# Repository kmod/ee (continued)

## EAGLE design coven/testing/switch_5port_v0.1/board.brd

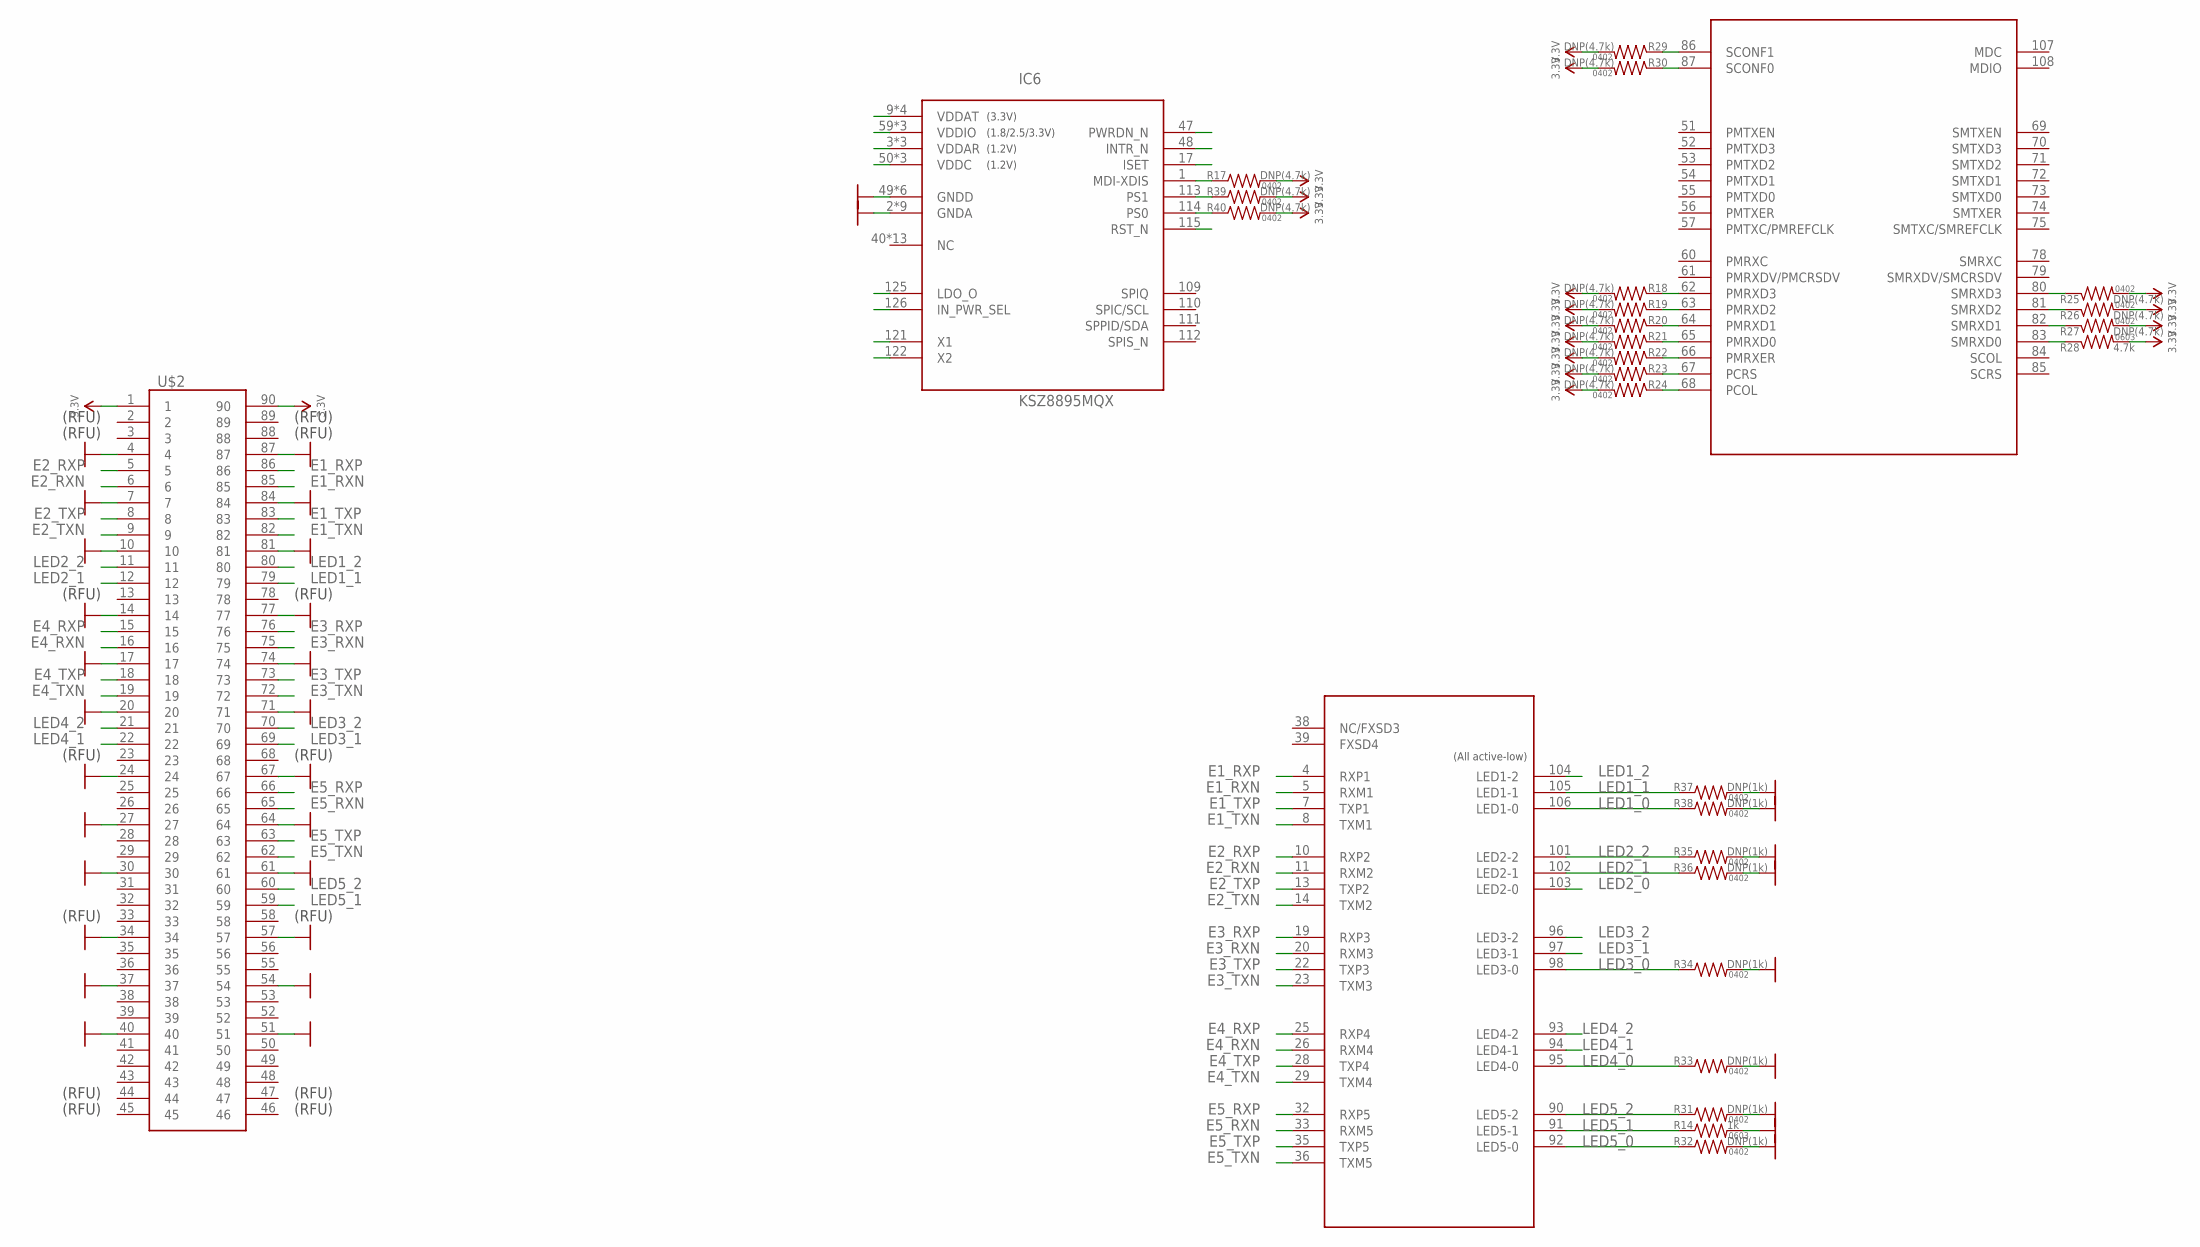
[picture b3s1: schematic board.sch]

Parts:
IC6: KSZ8895MQX; PQFP-128
R14: 1k; 0603-RES
R17, R18, R19, R20, R21, R22, R23, R24, R25, R26, R27, R29, R30, R39, R40: DNP(4.7k); 0402-RES
R28: 4.7k; 0603-RES
R31, R32, R33, R34, R35, R36, R37, R38: DNP(1k); 0402-RES
U$2: DF40-90HDR; DF40-HDR-90

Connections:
3.3V: R17.2, R18.2, R19.2, R20.2, R21.2, R22.2, R23.2, R24.2, R25.2, R26.2, R27.2, R28.2, R29.2, R30.2, R39.2, R40.2, U$2.1, U$2.90
E1_RXN: IC6.5 (RXM1), U$2.85
E1_RXP: IC6.4 (RXP1), U$2.86
E1_TXN: IC6.8 (TXM1), U$2.82
E1_TXP: IC6.7 (TXP1), U$2.83
E2_RXN: IC6.11 (RXM2), U$2.6
E2_RXP: IC6.10 (RXP2), U$2.5
E2_TXN: IC6.14 (TXM2), U$2.9
E2_TXP: IC6.13 (TXP2), U$2.8
E3_RXN: IC6.20 (RXM3), U$2.75
E3_RXP: IC6.19 (RXP3), U$2.76
E3_TXN: IC6.23 (TXM3), U$2.72
E3_TXP: IC6.22 (TXP3), U$2.73
E4_RXN: IC6.26 (RXM4), U$2.16
E4_RXP: IC6.25 (RXP4), U$2.15
E4_TXN: IC6.29 (TXM4), U$2.19
E4_TXP: IC6.28 (TXP4), U$2.18
E5_RXN: IC6.33 (RXM5), U$2.65
E5_RXP: IC6.32 (RXP5), U$2.66
E5_TXN: IC6.36 (TXM5), U$2.62
E5_TXP: IC6.35 (TXP5), U$2.63
GND: IC6.2 (GNDA), IC6.6 (GNDA), IC6.12 (GNDA), IC6.16 (GNDA), IC6.21 (GNDA), IC6.27 (GNDA), IC6.30 (GNDA), IC6.34 (GNDA), IC6.49 (GNDD), IC6.58 (GNDD), IC6.76 (GNDD), IC6.88 (GNDD), IC6.99 (GNDD), IC6.116 (GNDD), IC6.127 (GNDA), R14.2, R31.2, R32.2, R33.2, R34.2, R35.2, R36.2, R37.2, R38.2, U$2.4, U$2.7, U$2.10, U$2.14, U$2.17, U$2.20, U$2.24, U$2.27, U$2.30, U$2.34, U$2.37, U$2.40, U$2.51, U$2.54, U$2.57, U$2.61, U$2.64, U$2.67, U$2.71, U$2.74, U$2.77, U$2.81, U$2.84, U$2.87
LED1_0: IC6.106 (LED1-0), R38.1
LED1_1: IC6.105 (LED1-1), R37.1, U$2.79
LED1_2: IC6.104 (LED1-2), U$2.80
LED2_0: IC6.103 (LED2-0)
LED2_1: IC6.102 (LED2-1), R36.1, U$2.12
LED2_2: IC6.101 (LED2-2), R35.1, U$2.11
LED3_0: IC6.98 (LED3-0), R34.1
LED3_1: IC6.97 (LED3-1), U$2.69
LED3_2: IC6.96 (LED3-2), U$2.70
LED4_0: IC6.95 (LED4-0), R33.1
LED4_1: IC6.94 (LED4-1), U$2.22
LED4_2: IC6.93 (LED4-2), U$2.21
LED5_0: IC6.92 (LED5-0), R32.1
LED5_1: IC6.91 (LED5-1), R14.1, U$2.59
LED5_2: IC6.90 (LED5-2), R31.1, U$2.60
unnamed: IC6.1 (MDI-XDIS), R17.1
unnamed: IC6.62 (PMRXD3), R18.1
unnamed: IC6.63 (PMRXD2), R19.1
unnamed: IC6.64 (PMRXD1), R20.1
unnamed: IC6.65 (PMRXD0), R21.1
unnamed: IC6.66 (PMRXER), R22.1
unnamed: IC6.67 (PCRS), R23.1
unnamed: IC6.68 (PCOL), R24.1
unnamed: IC6.80 (SMRXD3), R25.1
unnamed: IC6.81 (SMRXD2), R26.1
unnamed: IC6.82 (SMRXD1), R27.1
unnamed: IC6.83 (SMRXD0), R28.1
unnamed: IC6.86 (SCONF1), R29.1
unnamed: IC6.87 (SCONF0), R30.1
unnamed: IC6.113 (PS1), R39.1
unnamed: IC6.114 (PS0), R40.1
unnamed: IC6.50 (VDDC), IC6.89 (VDDC), IC6.117 (VDDC)
unnamed: IC6.3 (VDDAR), IC6.15 (VDDAR), IC6.31 (VDDAR)
unnamed: IC6.59 (VDDIO), IC6.77 (VDDIO), IC6.100 (VDDIO)
unnamed: IC6.9 (VDDAT), IC6.18 (VDDAT), IC6.24 (VDDAT), IC6.37 (VDDAT)

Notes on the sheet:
(RFU)

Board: 4 copper layers, 27 parts (1 on the bottom side), 56 nets, no tracks yet.

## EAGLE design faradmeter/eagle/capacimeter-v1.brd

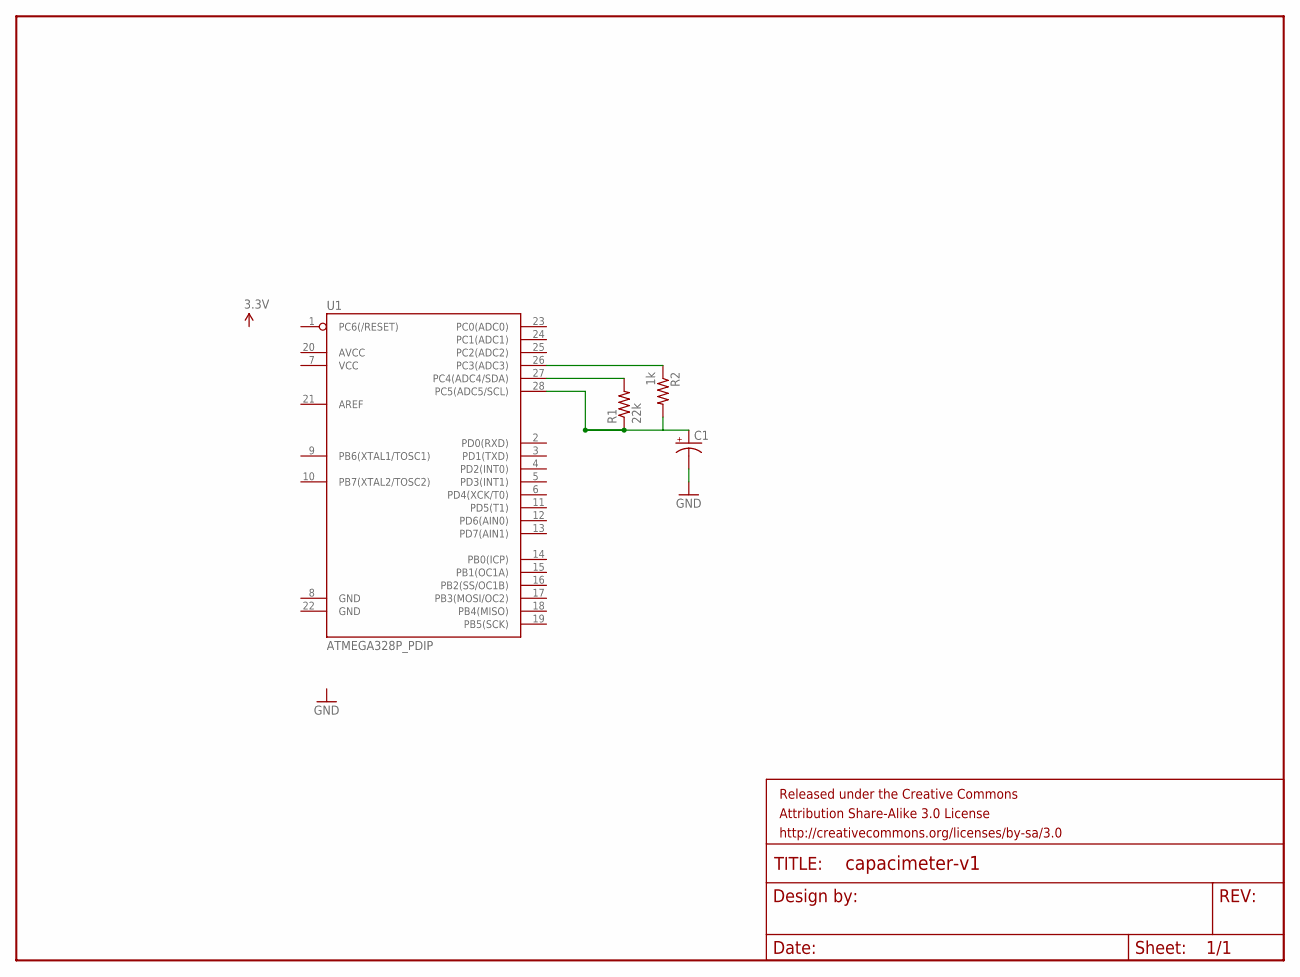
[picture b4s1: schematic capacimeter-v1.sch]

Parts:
C1: CAP_POL1206; EIA3216
FRAME1: FRAME-LETTER; CREATIVE_COMMONS
R1: 22k; 0603-RES
R2: 1k; 0603-RES
U1: ATMEGA328P_PDIP; DIL28-3

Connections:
GND: C1.C (-)
unnamed: R1.2, U1.27 (PC4(ADC4/SDA))
unnamed: C1.A (+), R1.1, R2.2, U1.28 (PC5(ADC5/SCL))
unnamed: R2.1, U1.26 (PC3(ADC3))

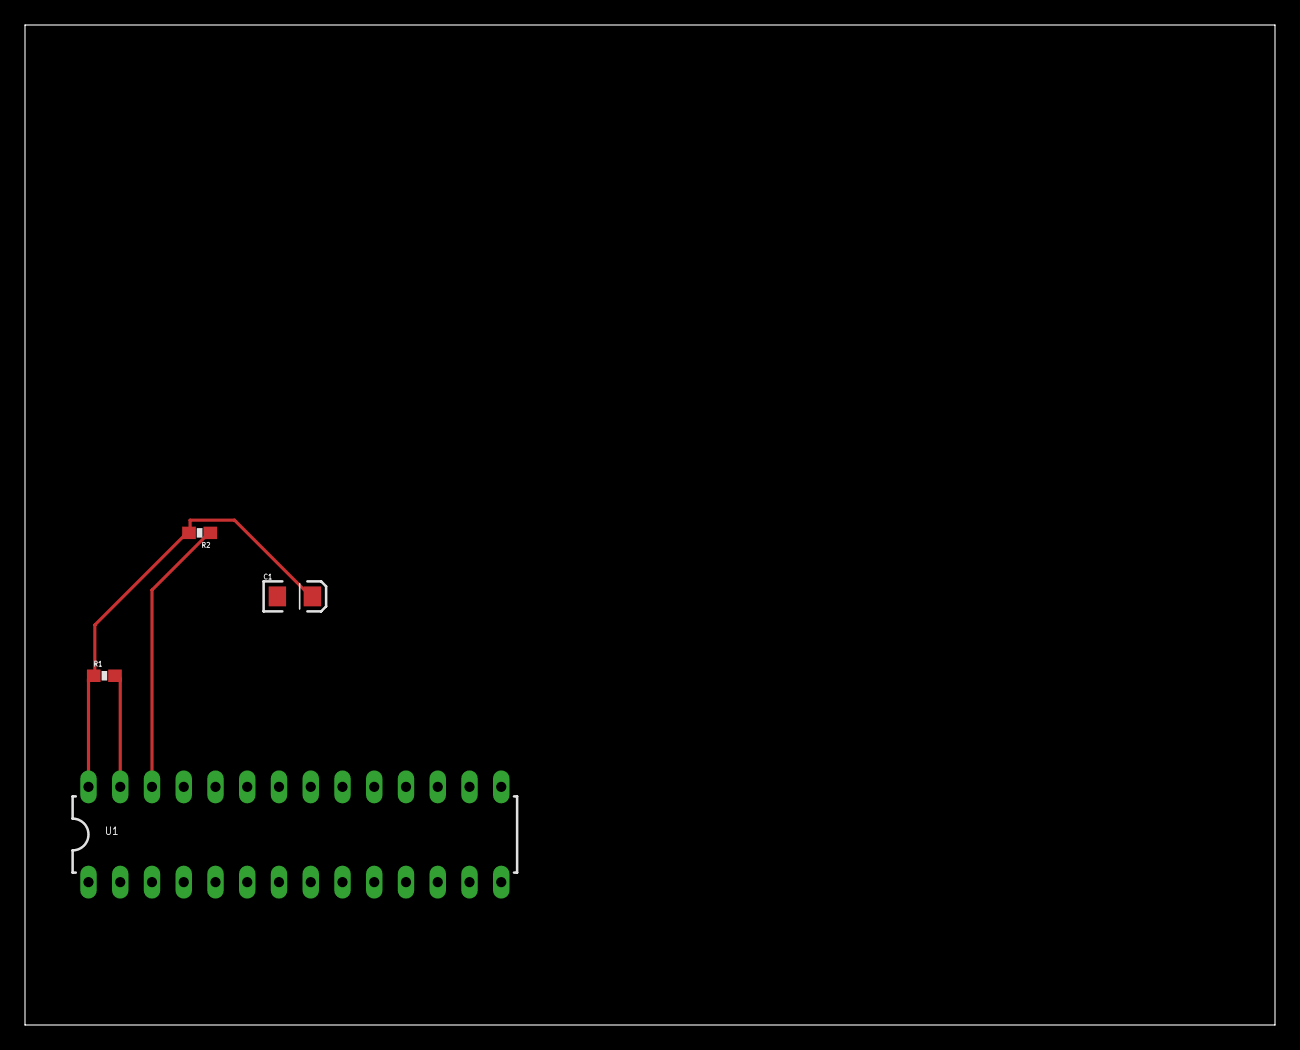
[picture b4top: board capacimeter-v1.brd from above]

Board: 2 copper layers, 100.0 x 80.0 mm, 5 parts (0 on the bottom side), 3 nets.

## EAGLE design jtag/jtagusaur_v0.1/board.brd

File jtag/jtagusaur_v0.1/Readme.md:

simple MB jtag board; bad footprint, use 0.1a instead

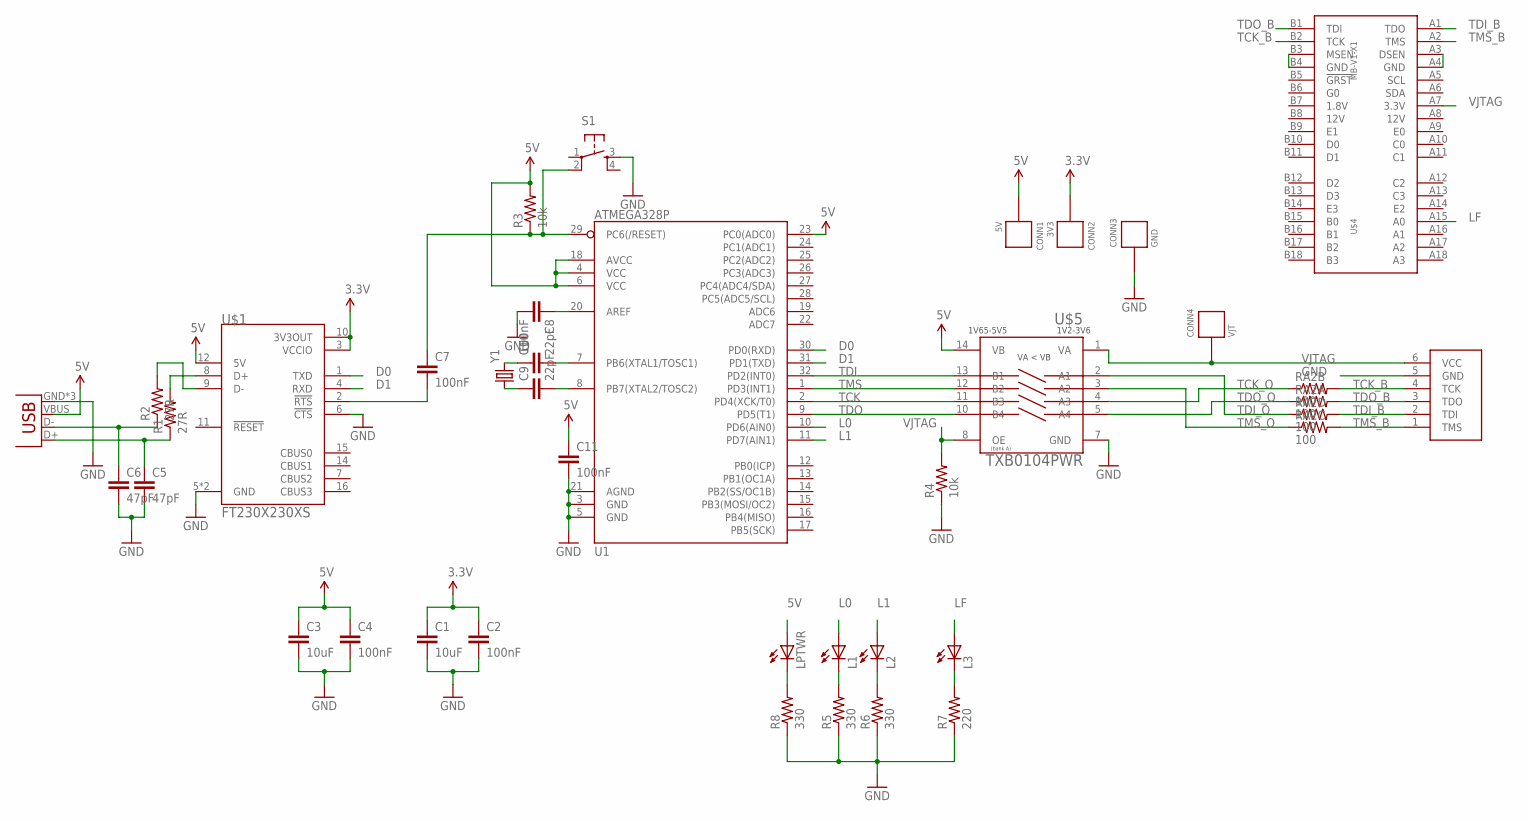
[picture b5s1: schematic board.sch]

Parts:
C1, C3: 10uF; 0805
C2, C4, C7, C8, C11: 100nF; 0402-CAP
C5, C6: 47pF; 0402-CAP
C9, C10: 22pF; 0402-CAP
CONN1: 5V; HOLE_22AWG
CONN2: 3V3; HOLE_22AWG
CONN3: GND; HOLE_22AWG
CONN4: VJT; HOLE_22AWG
JP1: USB-MICROB
L1, L2, L3: LED0603; 0603_LED
LPTWR: LED0603; 0603_LED
R1, R2: 27R; 0603-RES
R3, R4: 10k; 0603-RES
R5, R6, R8: 330; 0603-RES
R7: 220; 0603-RES
RA2: 100; 0603-ARV
S1: TAC_SWITCHPTH; TACTILE-PTH
U1: ATMEGA328P; TQFP32-08
U$1: FT230X230XS; SO16
U$2: JTAGDIGILENT; 1X06
U$4: MB-V1-X1; PCIE-X1-EDGE
U$5: TXB0104PWR; TSSOP14
Y1: CRYSTALHC49US; HC49US

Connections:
3.3V: C1.1, C2.1, CONN2.P, U$1.3 (VCCIO), U$1.10 (3V3OUT)
5V: C3.1, C4.1, C11.1, CONN1.P, JP1.VBUS, LPTWR.A, R3.2, U1.4 (VCC), U1.6 (VCC), U1.18 (AVCC), U1.23 (PC0(ADC0)), U$1.12 (5V), U$5.14 (VB)
D0: U1.30 (PD0(RXD)), U$1.1 (TXD)
D1: U1.31 (PD1(TXD)), U$1.4 (RXD)
GND: C1.2, C2.2, C3.2, C4.2, C5.2, C6.2, C8.2, C11.2, CONN3.P, JP1.GND, JP1.MT1 (GND), JP1.MT2 (GND), R4.1, R5.1, R6.1, R7.1, R8.1, S1.3, U1.3 (GND), U1.5 (GND), U1.21 (AGND), U$1.5 (GND), U$1.6 (!CTS), U$1.13 (GND), U$2.5 (GND), U$4.A3 (DSEN), U$4.A4 (GND), U$4.B3 (MSEN), U$4.B4 (GND)
L0: L1.A, U1.10 (PD6(AIN0))
L1: L2.A, U1.11 (PD7(AIN1))
LF: L3.A, U$4.A15 (A0)
LPWR: LPTWR.C, R8.2
unnamed: R1.2, U$1.8 (D+)
unnamed: R2.2, U$1.9 (D-)
unnamed: C6.1, JP1.D-, R2.1
unnamed: C5.1, JP1.D+, R1.1
unnamed: C7.2, U$1.2 (!RTS)
unnamed: C7.1, R3.1, S1.2, U1.29 (PC6(/RESET))
unnamed: C10.2, U1.7 (PB6(XTAL1/TOSC1))
unnamed: C8.1, U1.20 (AREF)
unnamed: C10.1, Y1.2
unnamed: C9.2, U1.8 (PB7(XTAL2/TOSC2))
unnamed: C9.1, Y1.1
unnamed: L1.C, R5.2
unnamed: L2.C, R6.2
unnamed: L3.C, R7.2
TCK: U1.2 (PD4(XCK/T0)), U$5.11 (B3)
TCK_B: RA2.7 (2), U$2.4 (TCK), U$4.B2 (TCK)
TCK_O: RA2.2 (1), U$5.4 (A3)
TDI: U1.32 (PD2(INT0)), U$5.13 (B1)
TDI_B: RA2.5 (2), U$2.2 (TDI), U$4.A1 (TDO)
TDI_O: RA2.4 (1), U$5.2 (A1)
TDO: U1.9 (PD5(T1)), U$5.10 (B4)
TDO_B: RA2.8 (2), U$2.3 (TDO), U$4.B1 (TDI)
TDO_O: RA2.1, U$5.5 (A4)
TMS: U1.1 (PD3(INT1)), U$5.12 (B2)
TMS_B: RA2.6 (2), U$2.1 (TMS), U$4.A2 (TMS)
TMS_O: RA2.3 (1), U$5.3 (A2)
VJTAG: CONN4.P, R4.2, U$2.6 (VCC), U$4.A7 (3.3V), U$5.1 (VA)

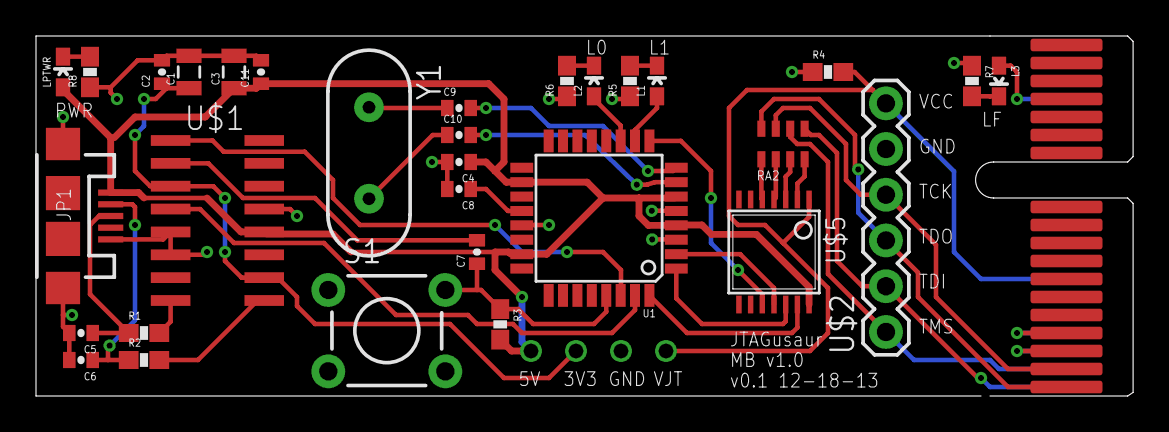
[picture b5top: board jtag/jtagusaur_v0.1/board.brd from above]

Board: 2 copper layers, 61.0 x 20.0 mm, 36 parts (0 on the bottom side), 36 nets.

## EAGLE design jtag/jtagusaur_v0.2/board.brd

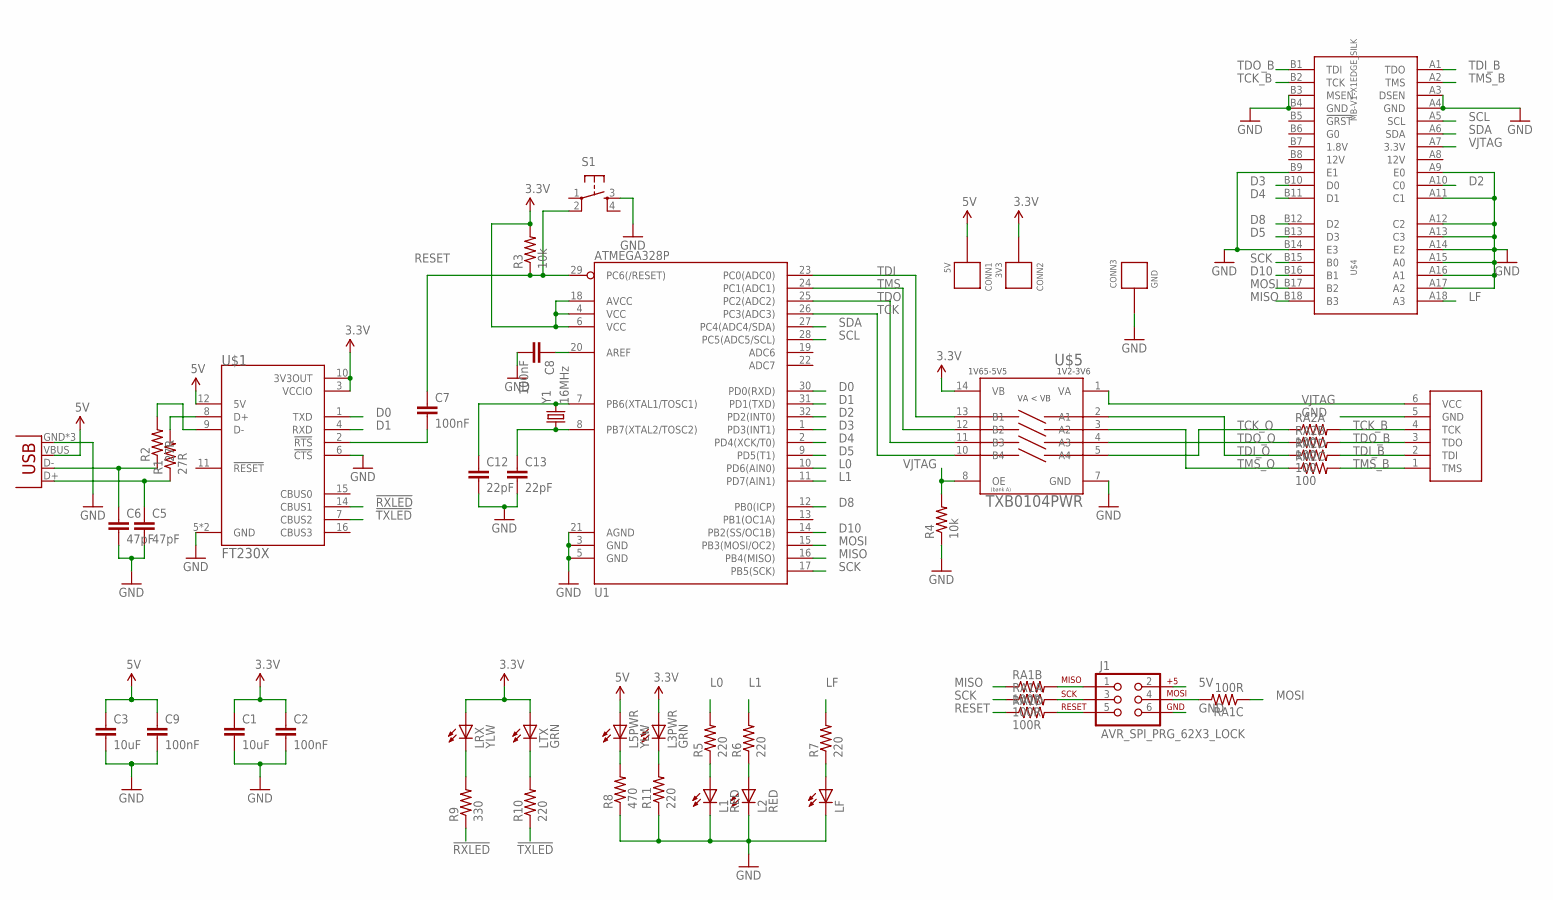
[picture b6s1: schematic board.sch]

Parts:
C1, C3: 10uF; 0805
C2, C7, C8, C9: 100nF; 0402-CAP
C5, C6: 47pF; 0402-CAP
C12, C13: 22pF; 0402-CAP
CONN1: 5V; HOLE_22AWG
CONN2: 3V3; HOLE_22AWG
CONN3: GND; HOLE_22AWG
J1: AVR_SPI_PRG_62X3_LOCK; 2X3_LOCK
JP1: USB-MICROB
L1, L2: RED; 0603_LED
L3PWR: GRN; 0603_LED
L5PWR: YLW; 0603_LED
LF: LED0603; 0603_LED
LRX: YLW; 0603_LED
LTX: GRN; 0603_LED
R1, R2: 27R; 0603-RES
R3, R4: 10k; 0603-RES
R5, R6, R7, R10, R11: 220; 0603-RES
R8: 470; 0603-RES
R9: 330; 0603-RES
RA1: 100R; 0603-ARV
RA2: 100; 0603-ARV
S1: TAC_SWITCHPTH; TACTILE-PTH
U1: ATMEGA328P; TQFP32-08
U$1: FT230X; TSSOP16
U$2: JTAGDIGILENT; 1X06
U$4: MB-V1-X1EDGE_SILK; MB-V1-X1-EDGE
U$5: TXB0104PWR; TSSOP14
Y1: 16MHz; HC49US

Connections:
3.3V: C1.1, C2.1, CONN2.P, L3PWR.A, LRX.A, LTX.A, R3.2, U1.4 (VCC), U1.6 (VCC), U1.18 (AVCC), U$1.3 (VCCIO), U$1.10 (3V3OUT), U$5.14 (VB)
5V: C3.1, C9.1, CONN1.P, J1.2, JP1.VBUS, L5PWR.A, U$1.12 (5V)
!RXLED: R9.1, U$1.14 (CBUS1)
!TXLED: R10.1, U$1.7 (CBUS2)
D0: U1.30 (PD0(RXD)), U$1.1 (TXD)
D1: U1.31 (PD1(TXD)), U$1.4 (RXD)
D2: U1.32 (PD2(INT0)), U$4.A10 (C0)
D3: U1.1 (PD3(INT1)), U$4.B10 (D0)
D4: U1.2 (PD4(XCK/T0)), U$4.B11 (D1)
D5: U1.9 (PD5(T1)), U$4.B13 (D3)
D8: U1.12 (PB0(ICP)), U$4.B12 (D2)
D10: U1.14 (PB2(SS/OC1B)), U$4.B16 (B1)
GND: C1.2, C2.2, C3.2, C5.2, C6.2, C8.2, C9.2, C12.2, C13.2, CONN3.P, J1.6, JP1.GND, JP1.MT1 (GND), JP1.MT2 (GND), L1.C, L2.C, LF.C, R4.1, R8.1, R11.1, S1.3, U1.3 (GND), U1.5 (GND), U1.21 (AGND), U$1.5 (GND), U$1.6 (!CTS), U$1.13 (GND), U$2.5 (GND), U$4.A3 (DSEN), U$4.A4 (GND), U$4.A9 (E0), U$4.A11 (C1), U$4.A12 (C2), U$4.A13 (C3), U$4.A14 (E2), U$4.A15 (A0), U$4.A16 (A1), U$4.A17 (A2), U$4.B3 (MSEN), U$4.B4 (GND), U$4.B9 (E1), U$4.B14 (E3), U$5.7 (GND)
L0: R5.2, U1.10 (PD6(AIN0))
L1: R6.2, U1.11 (PD7(AIN1))
LF: R7.2, U$4.A18 (A3)
MISO: RA1.2 (1), U1.16 (PB4(MISO)), U$4.B18 (B3)
MOSI: RA1.3 (1), U1.15 (PB3(MOSI/OC2)), U$4.B17 (B2)
unnamed: R1.2, U$1.8 (D+)
unnamed: R2.2, U$1.9 (D-)
unnamed: C6.1, JP1.D-, R2.1
unnamed: C5.1, JP1.D+, R1.1
unnamed: C7.2, U$1.2 (!RTS)
unnamed: L1.A, R5.1
unnamed: C12.1, U1.7 (PB6(XTAL1/TOSC1)), Y1.2
unnamed: C8.1, U1.20 (AREF)
unnamed: J1.1, RA1.7 (2)
unnamed: C13.1, U1.8 (PB7(XTAL2/TOSC2)), Y1.1
unnamed: L5PWR.C, R8.2
unnamed: L2.A, R6.1
unnamed: LF.A, R7.1
unnamed: LRX.C, R9.2
unnamed: LTX.C, R10.2
unnamed: J1.4, RA1.6 (2)
unnamed: L3PWR.C, R11.2
unnamed: J1.5, RA1.5 (2)
unnamed: J1.3, RA1.8 (2)
RESET: C7.1, R3.1, RA1.4 (1), S1.2, U1.29 (PC6(/RESET))
SCK: RA1.1, U1.17 (PB5(SCK)), U$4.B15 (B0)
SCL: U1.28 (PC5(ADC5/SCL)), U$4.A5 (SCL)
SDA: U1.27 (PC4(ADC4/SDA)), U$4.A6 (SDA)
TCK: U1.26 (PC3(ADC3)), U$5.10 (B4)
TCK_B: RA2.8 (2), U$2.4 (TCK), U$4.B2 (TCK)
TCK_O: RA2.1, U$5.5 (A4)
TDI: U1.23 (PC0(ADC0)), U$5.13 (B1)
TDI_B: RA2.5 (2), U$2.2 (TDI), U$4.A1 (TDO)
TDI_O: RA2.4 (1), U$5.2 (A1)
TDO: U1.25 (PC2(ADC2)), U$5.11 (B3)
TDO_B: RA2.7 (2), U$2.3 (TDO), U$4.B1 (TDI)
TDO_O: RA2.2 (1), U$5.4 (A3)
TMS: U1.24 (PC1(ADC1)), U$5.12 (B2)
TMS_B: RA2.6 (2), U$2.1 (TMS), U$4.A2 (TMS)
TMS_O: RA2.3 (1), U$5.3 (A2)
VJTAG: R4.2, U$2.6 (VCC), U$4.A7 (3.3V), U$5.1 (VA), U$5.8 (OE)

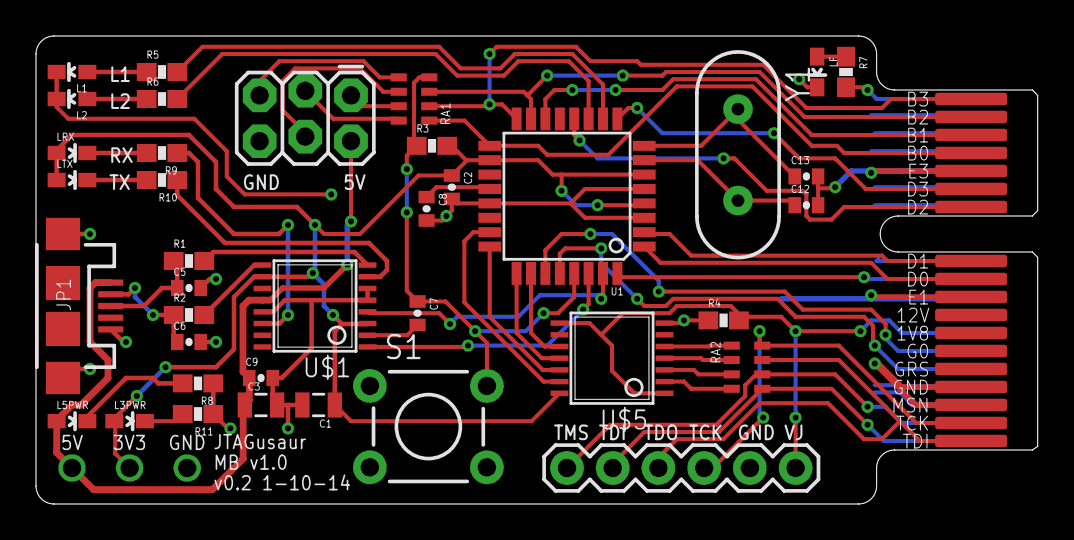
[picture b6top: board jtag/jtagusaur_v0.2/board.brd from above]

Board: 2 copper layers, 55.6 x 26.0 mm, 42 parts (0 on the bottom side), 54 nets.
